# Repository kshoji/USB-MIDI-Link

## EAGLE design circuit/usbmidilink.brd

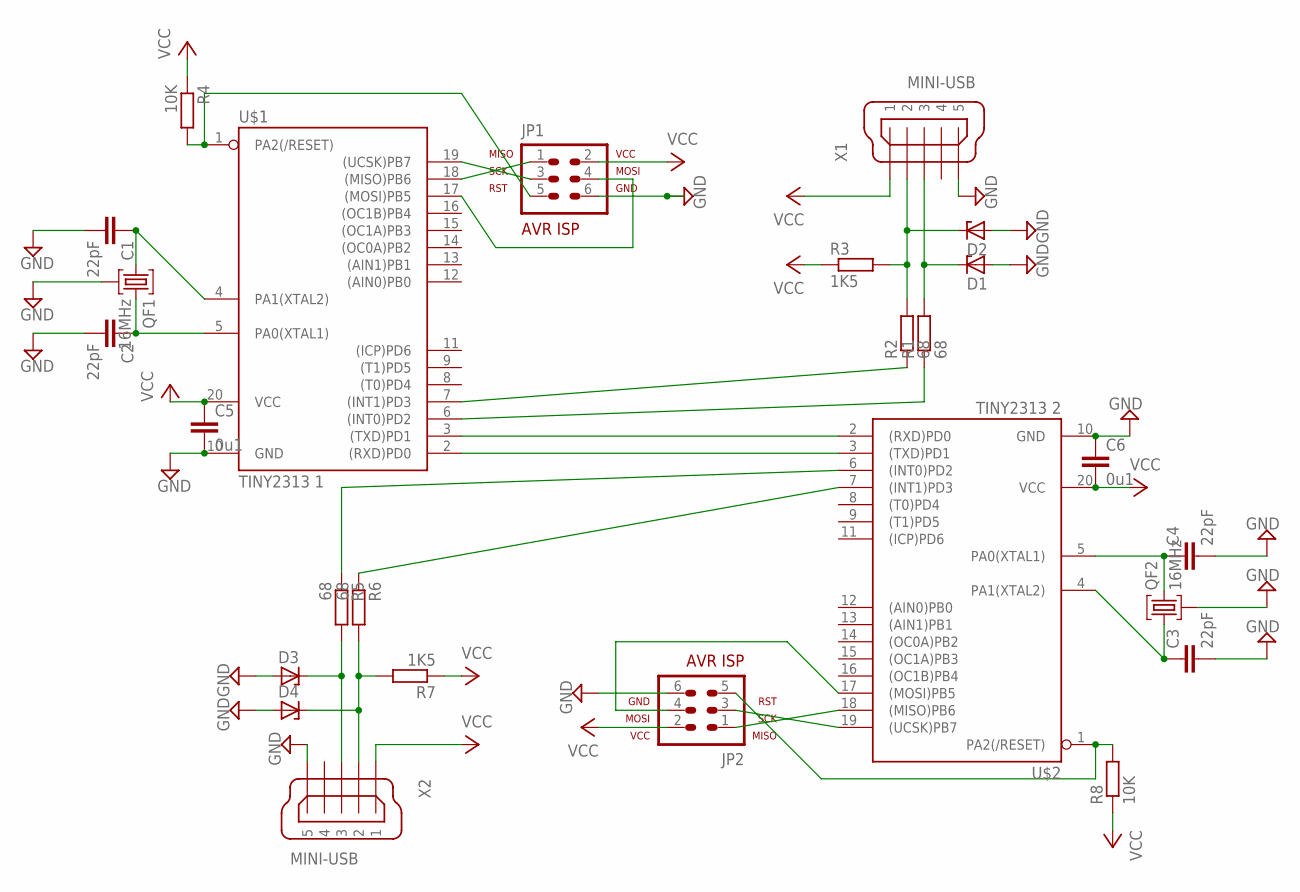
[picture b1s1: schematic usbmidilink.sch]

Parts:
C1, C2, C3, C4: 22pF; C2.5-4
C5, C6: 0u1; C2.5-4
D1, D2, D3, D4: ZENER-DIODEZD-5; ZDIO-5
JP1, JP2: AVR-ISP-6VERT; AVR-ISP-6
QF1, QF2: 16MHz; HC49U
R1, R2, R5, R6: 68; 0204/5
R3, R7: 1K5; 0204/5
R4, R8: 10K; 0204/5
U$1: TINY2313 1; DIL20
U$2: TINY2313 2; DIL20
X1, X2: MINI-USB; 32005-201

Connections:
GND: C1.2, C2.2, C3.2, C4.2, C5.2, C6.1, D1.A, D2.A, D3.A, D4.A, JP1.6, JP2.6, QF1.2, QF2.2, U$1.10 (GND), U$2.10 (GND), X1.5, X2.5
unnamed: R1.1, U$1.6 ((INT0)PD2)
unnamed: R2.1, U$1.7 ((INT1)PD3)
unnamed: C1.1, QF1.1, U$1.4 (PA1(XTAL2))
unnamed: C2.1, QF1.3, U$1.5 (PA0(XTAL1))
unnamed: D2.C, R2.2, R3.2, X1.2
unnamed: D1.C, R1.2, X1.3
unnamed: C3.1, QF2.1, U$2.4 (PA1(XTAL2))
unnamed: C4.1, QF2.3, U$2.5 (PA0(XTAL1))
unnamed: R6.1, U$2.7 ((INT1)PD3)
unnamed: R5.1, U$2.6 ((INT0)PD2)
unnamed: D4.C, R6.2, R7.2, X2.2
unnamed: D3.C, R5.2, X2.3
unnamed: U$1.2 ((RXD)PD0), U$2.3 ((TXD)PD1)
unnamed: U$1.3 ((TXD)PD1), U$2.2 ((RXD)PD0)
unnamed: JP2.1, U$2.18 ((MISO)PB6)
unnamed: JP1.3, U$1.19 ((UCSK)PB7)
unnamed: JP1.1, U$1.18 ((MISO)PB6)
unnamed: JP1.5, R4.2, U$1.1 (PA2(/RESET))
unnamed: JP1.4, U$1.17 ((MOSI)PB5)
unnamed: JP2.3, U$2.19 ((UCSK)PB7)
unnamed: JP2.5, R8.2, U$2.1 (PA2(/RESET))
unnamed: JP2.4, U$2.17 ((MOSI)PB5)
VCC: C5.1, C6.2, JP1.2, JP2.2, R3.1, R4.1, R7.1, R8.1, U$1.20 (VCC), U$2.20 (VCC), X1.1, X2.1

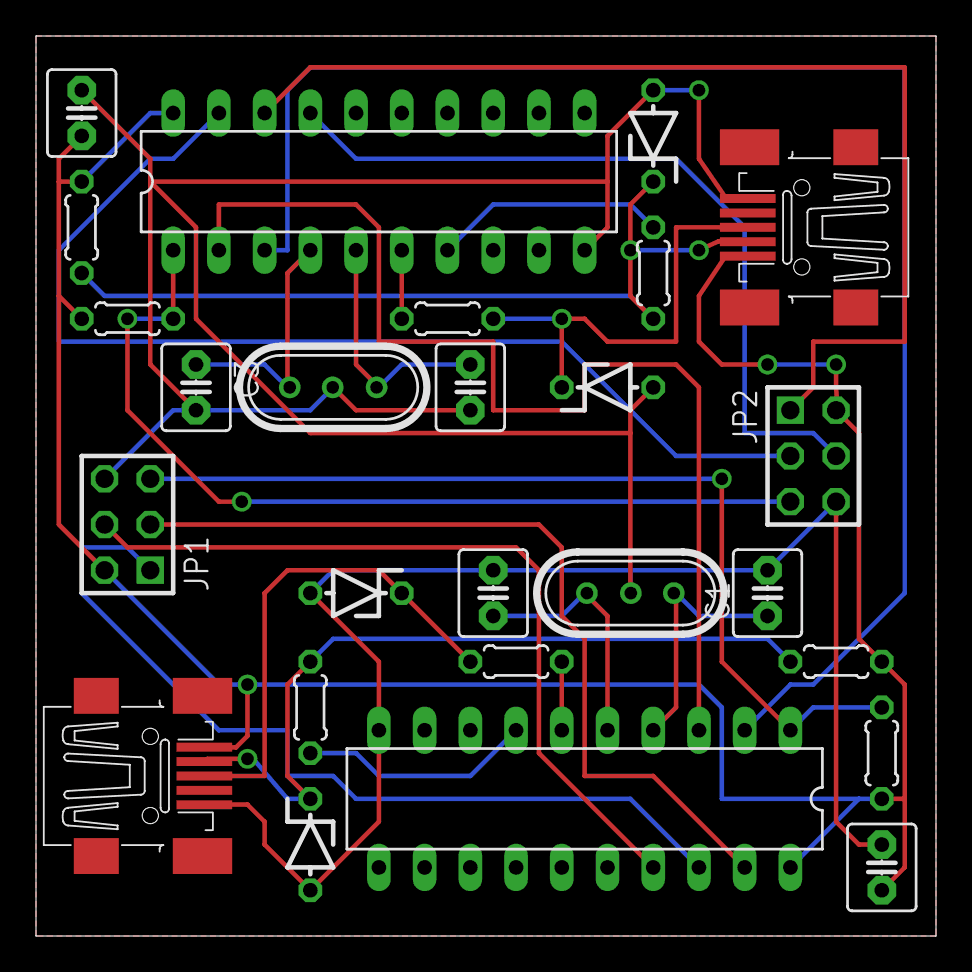
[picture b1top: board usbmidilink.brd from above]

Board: 2 copper layers, 50.0 x 50.0 mm, 26 parts (0 on the bottom side), 24 nets.

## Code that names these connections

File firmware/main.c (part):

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
/*
 PORT ASSIGN
 PD0: RxD (Serial MIDI)
 PD1: TxD (Serial MIDI)
 PD2: USB D+
 PD3: USB D-
 */

#define HW_CDC_BULK_OUT_SIZE     (8)
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
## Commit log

2012-11-02 first commit.
2012-11-02 Corrected license. V-USB's license is GPL, and commercial license. I chose GPL.

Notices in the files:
firmware/main.c:
(C) 2010 by morecat_lab (original: MICOMOCO http://morecatlab.akiba.coocan.jp/morecat_lab/MOCO.html)
(C) 2012 Kaoru Shoji (this version: https://github.com/kshoji/USB-MIDI-Link)
